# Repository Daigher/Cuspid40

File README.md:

# Cuspid40
The Cuspid40 is an ortholinear or alpha staggered 40% keyboard which features an XT column and a nav cluster. 
It's meant to be super affordable and easy to solder, just requiring an 0xCB Helios (or any other pro-micro compatible microcontrollers) and a bunch of 1N4148 tht diodes. 
<br><br>
The layout was originally ideated by xahy, while knave created the silkscreen art. The design takes inspirations from boards such as the BOX75, the Froggr and the Shinkansen. The gaps between the keys are purposefully meant to highlight the through hole diodes which are soldered on top of the PCB, and because of this the board is intended to be plateless and no plate files are provided in this repo.
<br><br>

<br><br>
At the moment this is purely a skeleton kit consisting of only the pcb and bottom plate, there are plans for a proper case.
<br><br>
To-Do list: 
- Test Firmware.
- Design 3D printable Case.

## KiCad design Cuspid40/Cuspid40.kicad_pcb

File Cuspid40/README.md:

# Cuspid40
 An alpha staggered/ortho 40% keyboard with a nav cluser and an xt column

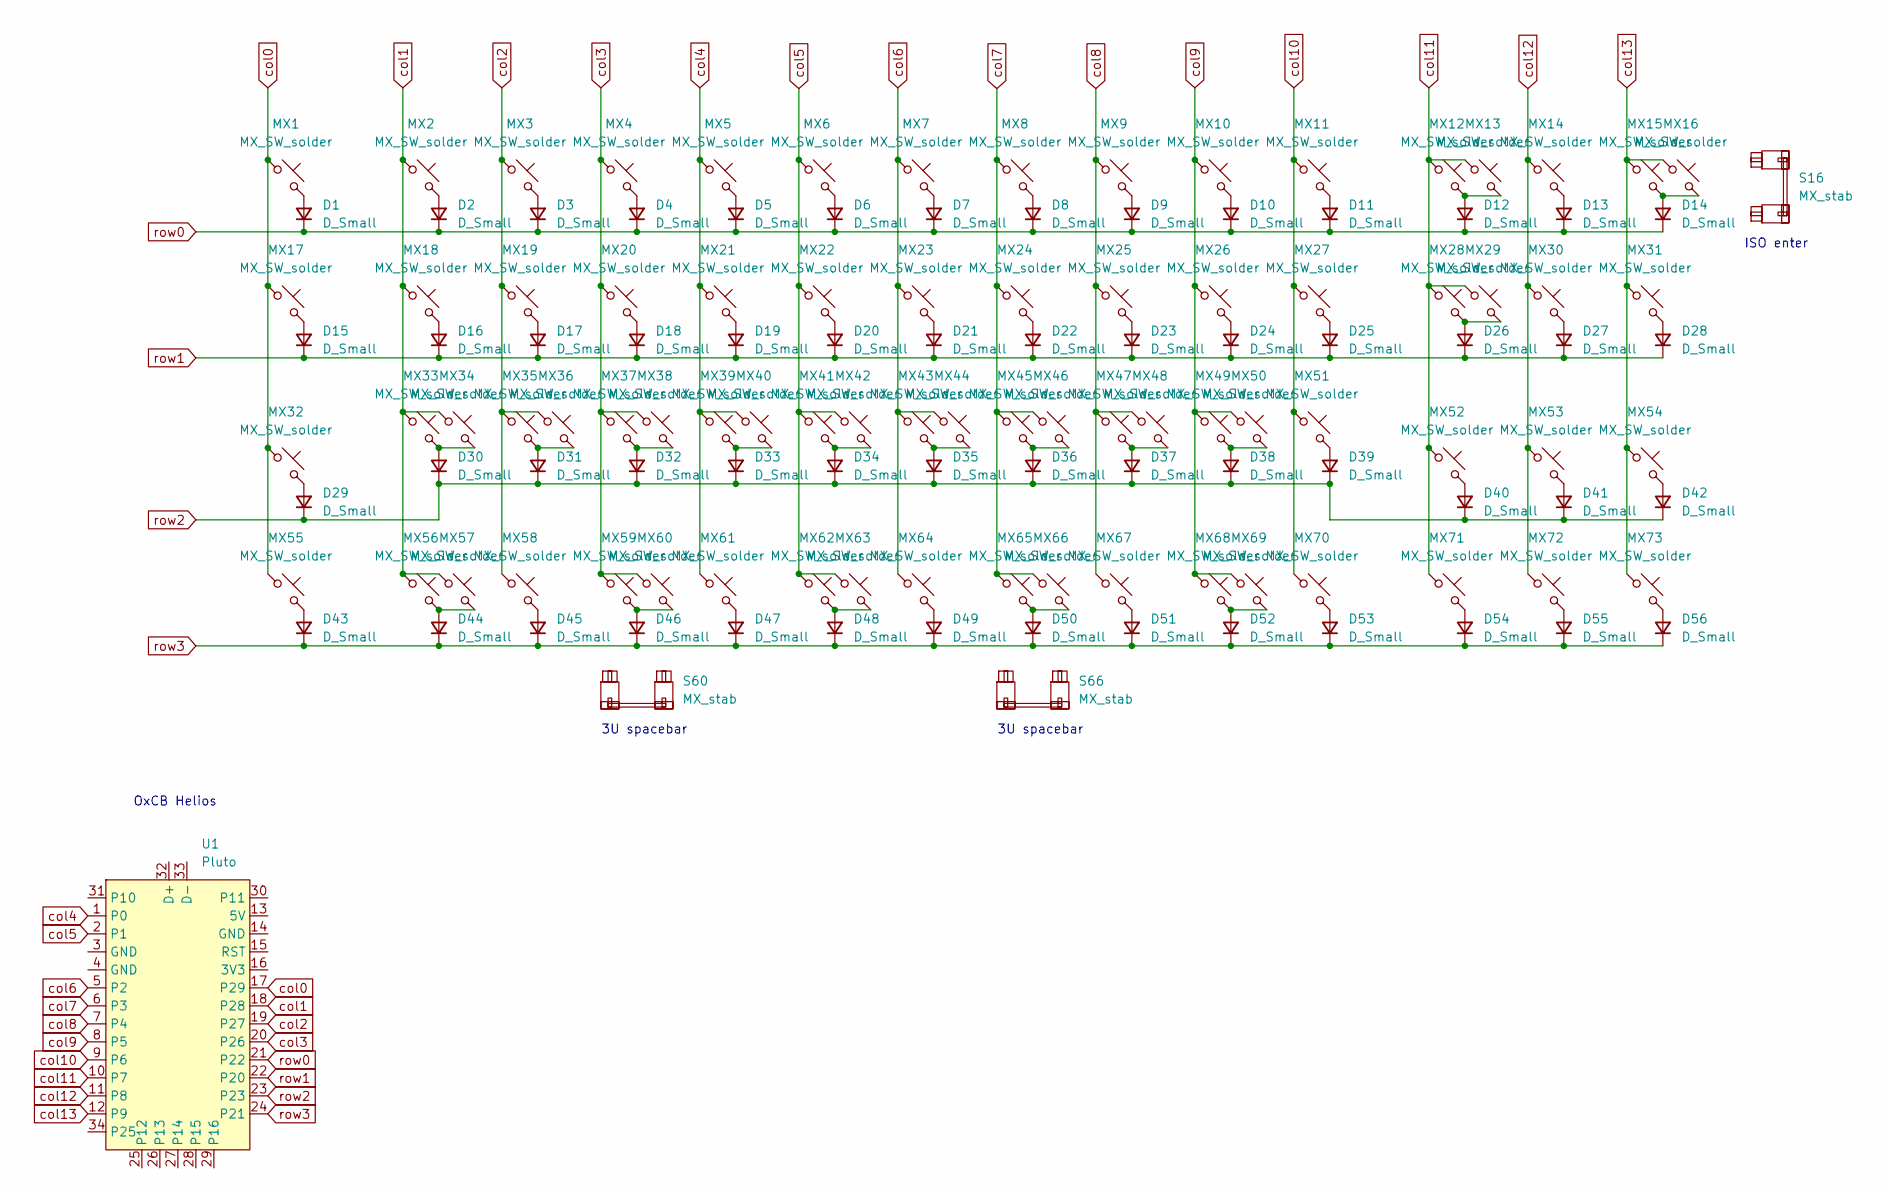
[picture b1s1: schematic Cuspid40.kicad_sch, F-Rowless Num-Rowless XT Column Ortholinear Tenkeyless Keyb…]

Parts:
D1, D2, D3, D4, D5, D6, D7, D8, D9, D10, D11, D12, D13, D14, D15, D16, D17, D18, D19, D20, D21, D22, D23, D24, D25, D26, D27, D28, D29, D30, D31, D32, D33, D34, D35, D36, D37, D38, D39, D40, D41, D42, D43, D44, D45, D46, D47, D48, D49, D50, D51, D52, D53, D54, D55, D56: D_Small; D_DO-35_SOD27_P5.08mm_Horizontal
MX1, MX2, MX3, MX4, MX5, MX6, MX7, MX8, MX9, MX10, MX11, MX12, MX14, MX15, MX16, MX17, MX18, MX19, MX20, MX21, MX22, MX23, MX24, MX25, MX26, MX27, MX29, MX30, MX31, MX32, MX33, MX35, MX36, MX37, MX38, MX39, MX40, MX41, MX42, MX43, MX44, MX45, MX46, MX47, MX48, MX49, MX51, MX52, MX53, MX54, MX55, MX56, MX58, MX59, MX60, MX61, MX62, MX63, MX64, MX65, MX66, MX67, MX68, MX70, MX71, MX72, MX73: MX_SW_solder; SW_MX_1u
MX13, MX34, MX50, MX57, MX69: MX_SW_solder; SW_MX_1.5u
MX28: MX_SW_solder; SW_MX_1.75u
S16: MX_stab; STAB_MX_P_ISO
S60, S66: MX_stab; STAB_MX_P_3u
U1: Pluto; Helios_AH_USBup

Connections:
unnamed: D1.2 (A), MX1.2
unnamed: D2.2 (A), MX2.2
unnamed: D3.2 (A), MX3.2
unnamed: D4.2 (A), MX4.2
unnamed: D5.2 (A), MX5.2
unnamed: D6.2 (A), MX6.2
unnamed: D7.2 (A), MX7.2
unnamed: D8.2 (A), MX8.2
unnamed: D9.2 (A), MX9.2
unnamed: D10.2 (A), MX10.2
unnamed: D11.2 (A), MX11.2
unnamed: D12.2 (A), MX12.2, MX13.2
unnamed: D13.2 (A), MX14.2
unnamed: D14.2 (A), MX15.2, MX16.2
unnamed: D15.2 (A), MX17.2
unnamed: D16.2 (A), MX18.2
unnamed: D17.2 (A), MX19.2
unnamed: D18.2 (A), MX20.2
unnamed: D19.2 (A), MX21.2
unnamed: D20.2 (A), MX22.2
unnamed: D21.2 (A), MX23.2
unnamed: D22.2 (A), MX24.2
unnamed: D23.2 (A), MX25.2
unnamed: D24.2 (A), MX26.2
unnamed: D25.2 (A), MX27.2
unnamed: D26.2 (A), MX28.2, MX29.2
unnamed: D27.2 (A), MX30.2
unnamed: D28.2 (A), MX31.2
unnamed: D29.2 (A), MX32.2
unnamed: D30.2 (A), MX33.2, MX34.2
unnamed: D31.2 (A), MX35.2, MX36.2
unnamed: D32.2 (A), MX37.2, MX38.2
unnamed: D33.2 (A), MX39.2, MX40.2
unnamed: D34.2 (A), MX41.2, MX42.2
unnamed: D35.2 (A), MX43.2, MX44.2
unnamed: D36.2 (A), MX45.2, MX46.2
unnamed: D37.2 (A), MX47.2, MX48.2
unnamed: D38.2 (A), MX49.2, MX50.2
unnamed: D39.2 (A), MX51.2
unnamed: D40.2 (A), MX52.2
unnamed: D41.2 (A), MX53.2
unnamed: D42.2 (A), MX54.2
unnamed: D43.2 (A), MX55.2
unnamed: D44.2 (A), MX56.2, MX57.2
unnamed: D45.2 (A), MX58.2
unnamed: D46.2 (A), MX59.2, MX60.2
unnamed: D47.2 (A), MX61.2
unnamed: D48.2 (A), MX62.2, MX63.2
unnamed: D49.2 (A), MX64.2
unnamed: D50.2 (A), MX65.2, MX66.2
unnamed: D51.2 (A), MX67.2
unnamed: D52.2 (A), MX68.2, MX69.2
unnamed: D53.2 (A), MX70.2
unnamed: D54.2 (A), MX71.2
unnamed: D55.2 (A), MX72.2
unnamed: D56.2 (A), MX73.2
col0: MX1.1, MX17.1, MX32.1, MX55.1, U1.17 (P29)
col1: MX2.1, MX18.1, MX33.1, MX34.1, MX56.1, MX57.1, U1.18 (P28)
col2: MX3.1, MX19.1, MX35.1, MX36.1, MX58.1, U1.19 (P27)
col3: MX4.1, MX20.1, MX37.1, MX38.1, MX59.1, MX60.1, U1.20 (P26)
col4: MX5.1, MX21.1, MX39.1, MX40.1, MX61.1, U1.1 (P0)
col5: MX6.1, MX22.1, MX41.1, MX42.1, MX62.1, MX63.1, U1.2 (P1)
col6: MX7.1, MX23.1, MX43.1, MX44.1, MX64.1, U1.5 (P2)
col7: MX8.1, MX24.1, MX45.1, MX46.1, MX65.1, MX66.1, U1.6 (P3)
col8: MX9.1, MX25.1, MX47.1, MX48.1, MX67.1, U1.7 (P4)
col9: MX10.1, MX26.1, MX49.1, MX50.1, MX68.1, MX69.1, U1.8 (P5)
col10: MX11.1, MX27.1, MX51.1, MX70.1, U1.9 (P6)
col11: MX12.1, MX13.1, MX28.1, MX29.1, MX52.1, MX71.1, U1.10 (P7)
col12: MX14.1, MX30.1, MX53.1, MX72.1, U1.11 (P8)
col13: MX15.1, MX16.1, MX31.1, MX54.1, MX73.1, U1.12 (P9)
row0: D1.1 (K), D2.1 (K), D3.1 (K), D4.1 (K), D5.1 (K), D6.1 (K), D7.1 (K), D8.1 (K), D9.1 (K), D10.1 (K), D11.1 (K), D12.1 (K), D13.1 (K), D14.1 (K), U1.21 (P22)
row1: D15.1 (K), D16.1 (K), D17.1 (K), D18.1 (K), D19.1 (K), D20.1 (K), D21.1 (K), D22.1 (K), D23.1 (K), D24.1 (K), D25.1 (K), D26.1 (K), D27.1 (K), D28.1 (K), U1.22 (P20)
row2: D29.1 (K), D30.1 (K), D31.1 (K), D32.1 (K), D33.1 (K), D34.1 (K), D35.1 (K), D36.1 (K), D37.1 (K), D38.1 (K), D39.1 (K), D40.1 (K), D41.1 (K), D42.1 (K), U1.23
row3: D43.1 (K), D44.1 (K), D45.1 (K), D46.1 (K), D47.1 (K), D48.1 (K), D49.1 (K), D50.1 (K), D51.1 (K), D52.1 (K), D53.1 (K), D54.1 (K), D55.1 (K), D56.1 (K), U1.24 (P21)

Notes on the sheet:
ISO enter
OxCB Helios
3U spacebar

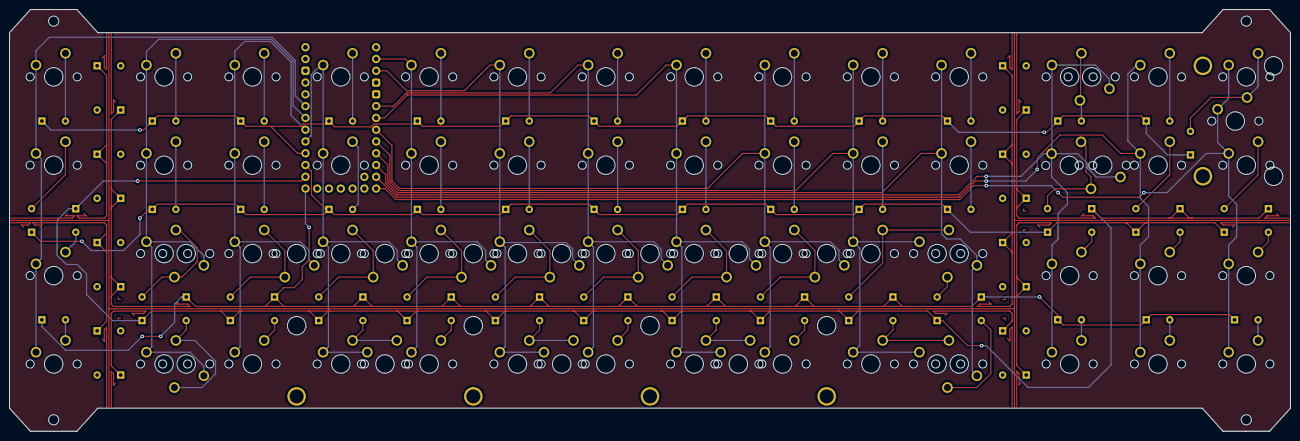
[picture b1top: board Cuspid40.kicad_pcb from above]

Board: 2 copper layers, 276.2 x 91.0 mm, 149 parts (1 on the bottom side), 74 nets.

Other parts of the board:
D: 3.6V; D_DO-35_SOD27_P5.08mm_Horizontal
D#2, D#3, D#4, D#5, D#6, D#7, D#8, D#9, D#10, D#11, D#12, D#13, D#14, D#15, D#16: 3.6V; D_DO-35_SOD27_P5.08mm_Horizontal

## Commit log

2024-05-13 Added the files
2024-05-13 Added Gerbers
2024-05-13 Production files folder
2024-05-15 Fixed small error in the silkscreen
2024-05-15 Create LICENSE
2025-03-20 Updated some files
2025-03-21 Updating some files.
2025-03-21 just some changes (i hate git)
